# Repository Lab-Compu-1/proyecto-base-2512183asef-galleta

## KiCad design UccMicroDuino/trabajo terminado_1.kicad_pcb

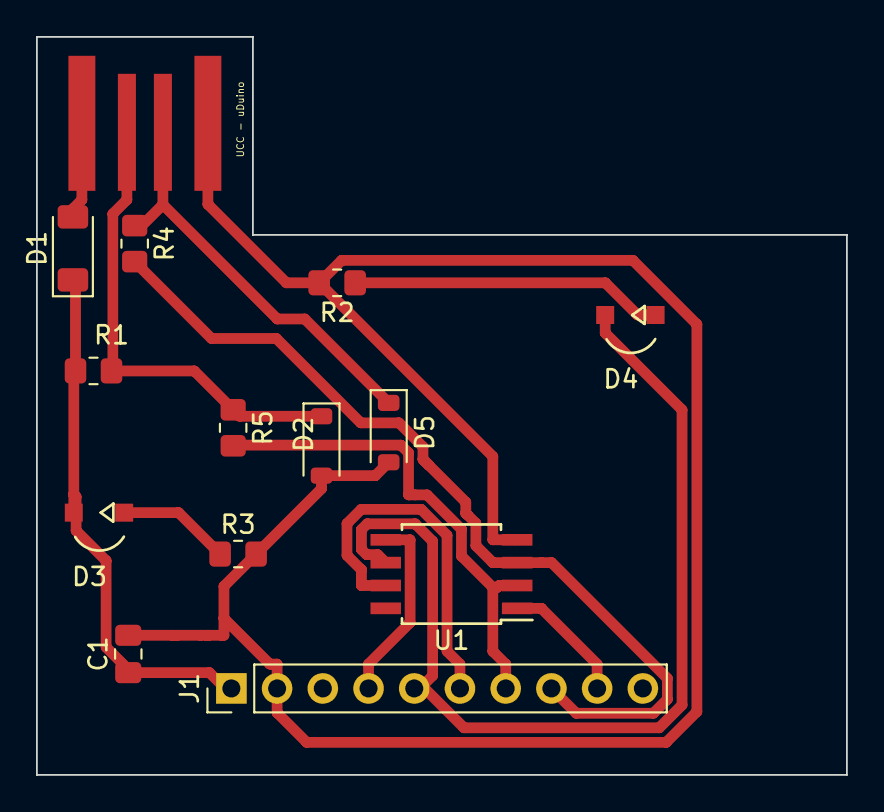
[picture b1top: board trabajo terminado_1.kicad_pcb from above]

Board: 2 copper layers, 45.0 x 41.0 mm, 14 parts (0 on the bottom side), 13 nets.

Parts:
C1: 0.1 u; C_0805_2012Metric_Pad1.18x1.45mm_HandSolder
D1: PMLL4148L; D_MiniMELF
D2, D5: 3.6V 1/2mW; D_SOD-123
D3: red led; ledSMD
D4: led green; ledSMD
J1: header; PinHeader_1x10_P2.54mm_Vertical
J2: PCB USB Type A; USB_A_UCC
R1: 1.5k ohms 5% 1/8W; R_0805_2012Metric_Pad1.20x1.40mm_HandSolder
R2, R3: 330 ohms 5% 1/8W; R_0805_2012Metric_Pad1.20x1.40mm_HandSolder
R4, R5: 68 ohms 5% 1/8W; R_0805_2012Metric_Pad1.20x1.40mm_HandSolder
U1: ATtiny85-20S; SOIC-8W_5.3x5.3mm_P1.27mm

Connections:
+5V: C1.1, D1.1 (K), D3.2 (A), J1.1, R1.1, U1.8 (VCC)
GND: C1.2, D2.2 (A), D5.2 (A), J1.2, J2.4 (GND), R2.2, R3.2, U1.4 (GND)
unnamed: D1.2 (A), J2.1 (VBUS)
unnamed: D2.1 (K), J2.2 (D-), R1.2, R5.1
unnamed: D3.1 (K), R3.1
unnamed: D4.2 (A), J1.5, U1.6 (PB1)
unnamed: D4.1 (K), R2.1
unnamed: D5.1 (K), J2.3 (D+), R4.1
unnamed: J1.4, U1.5 (AREF/PB0)
unnamed: J1.6, U1.7 (PB2)
unnamed: J1.7, R5.2, U1.2 (XTAL1/PB3)
unnamed: J1.8, R4.2, U1.3 (XTAL2/PB4)
unnamed: J1.9, U1.1 (~RESET/PB5)

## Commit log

2025-03-17 GitHub Classroom Feedback
2025-03-17 Setting up GitHub Classroom Feedback
2025-04-07 modificamos plano terminado el circuito
